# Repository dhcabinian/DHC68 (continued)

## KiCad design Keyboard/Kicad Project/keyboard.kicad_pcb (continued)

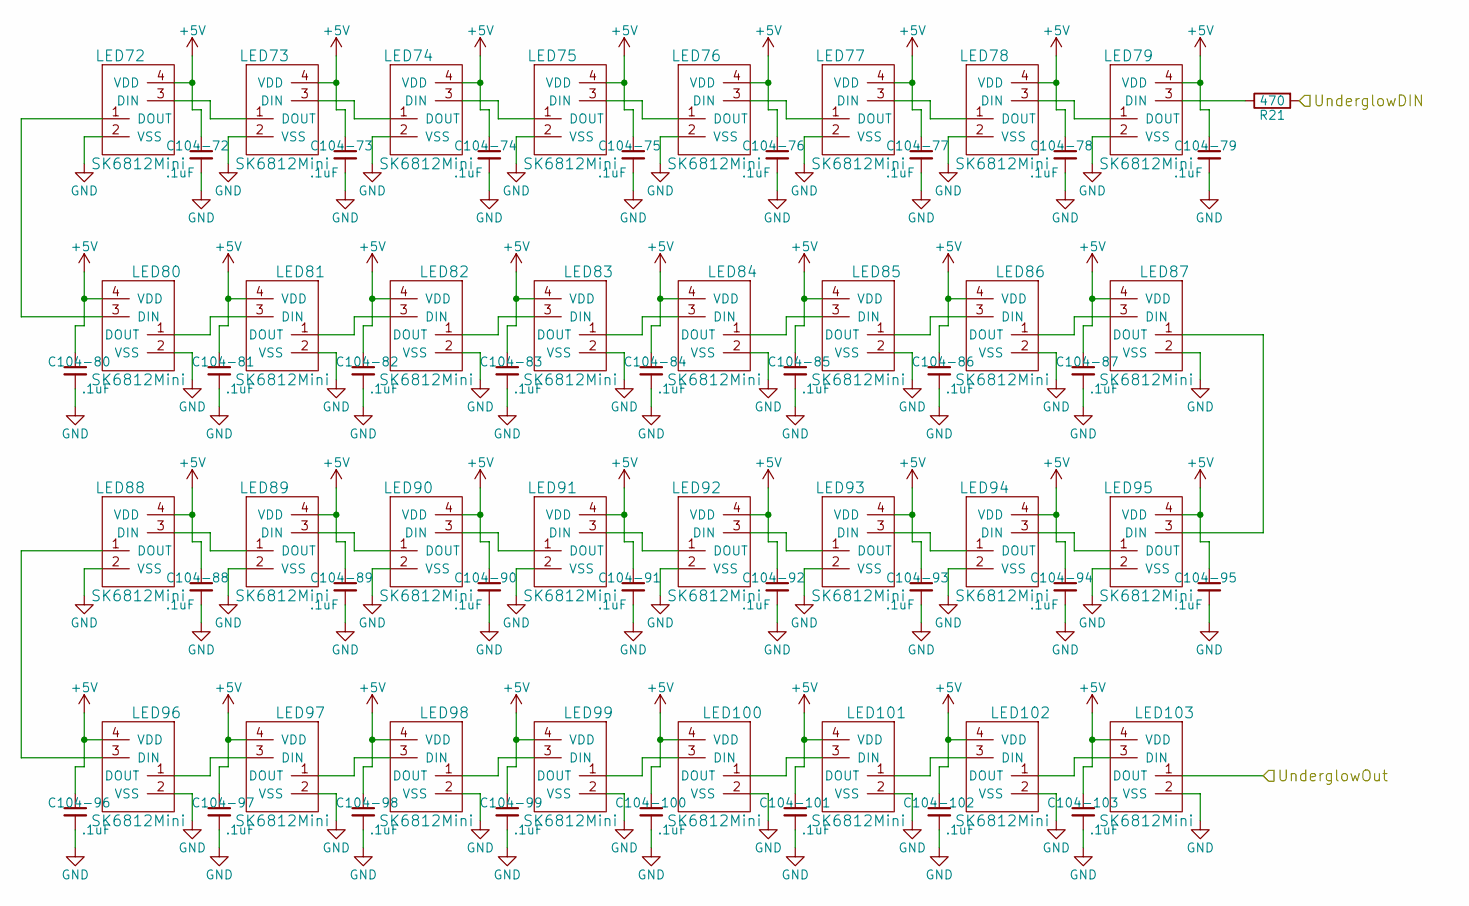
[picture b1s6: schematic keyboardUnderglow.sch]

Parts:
C104-72, C104-73, C104-74, C104-75, C104-76, C104-77, C104-78, C104-79, C104-80, C104-81, C104-82, C104-83, C104-84, C104-85, C104-86, C104-87, C104-88, C104-89, C104-90, C104-91, C104-92, C104-93, C104-94, C104-95, C104-96, C104-97, C104-98, C104-99, C104-100, C104-101, C104-102, C104-103: .1uF; 0805C
LED72, LED73, LED74, LED75, LED76, LED77, LED78, LED79, LED80, LED81, LED82, LED83, LED84, LED85, LED86, LED87, LED88, LED89, LED90, LED91, LED92, LED93, LED94, LED95, LED96, LED97, LED98, LED99, LED100, LED101, LED102, LED103: SK6812Mini; Sk6812Mini
R21: 470; 0805R

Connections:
+5V: C104-72.1, C104-73.1, C104-74.1, C104-75.1, C104-76.1, C104-77.1, C104-78.1, C104-79.1, C104-80.1, C104-81.1, C104-82.1, C104-83.1, C104-84.1, C104-85.1, C104-86.1, C104-87.1, C104-88.1, C104-89.1, C104-90.1, C104-91.1, C104-92.1, C104-93.1, C104-94.1, C104-95.1, C104-96.1, C104-97.1, C104-98.1, C104-99.1, C104-100.1, C104-101.1, C104-102.1, C104-103.1, LED72.4 (VDD), LED73.4 (VDD), LED74.4 (VDD), LED75.4 (VDD), LED76.4 (VDD), LED77.4 (VDD), LED78.4 (VDD), LED79.4 (VDD), LED80.4 (VDD), LED81.4 (VDD), LED82.4 (VDD), LED83.4 (VDD), LED84.4 (VDD), LED85.4 (VDD), LED86.4 (VDD), LED87.4 (VDD), LED88.4 (VDD), LED89.4 (VDD), LED90.4 (VDD), LED91.4 (VDD), LED92.4 (VDD), LED93.4 (VDD), LED94.4 (VDD), LED95.4 (VDD), LED96.4 (VDD), LED97.4 (VDD), LED98.4 (VDD), LED99.4 (VDD), LED100.4 (VDD), LED101.4 (VDD), LED102.4 (VDD), LED103.4 (VDD); also elsewhere on the board
/keyboardUnderglow/UnderglowDIN: R21.2; also elsewhere on the board
/keyboardUnderglow/UnderglowOut: LED103.1 (DOUT); also elsewhere on the board
GND: C104-72.2, C104-73.2, C104-74.2, C104-75.2, C104-76.2, C104-77.2, C104-78.2, C104-79.2, C104-80.2, C104-81.2, C104-82.2, C104-83.2, C104-84.2, C104-85.2, C104-86.2, C104-87.2, C104-88.2, C104-89.2, C104-90.2, C104-91.2, C104-92.2, C104-93.2, C104-94.2, C104-95.2, C104-96.2, C104-97.2, C104-98.2, C104-99.2, C104-100.2, C104-101.2, C104-102.2, C104-103.2, LED72.2 (VSS), LED73.2 (VSS), LED74.2 (VSS), LED75.2 (VSS), LED76.2 (VSS), LED77.2 (VSS), LED78.2 (VSS), LED79.2 (VSS), LED80.2 (VSS), LED81.2 (VSS), LED82.2 (VSS), LED83.2 (VSS), LED84.2 (VSS), LED85.2 (VSS), LED86.2 (VSS), LED87.2 (VSS), LED88.2 (VSS), LED89.2 (VSS), LED90.2 (VSS), LED91.2 (VSS), LED92.2 (VSS), LED93.2 (VSS), LED94.2 (VSS), LED95.2 (VSS), LED96.2 (VSS), LED97.2 (VSS), LED98.2 (VSS), LED99.2 (VSS), LED100.2 (VSS), LED101.2 (VSS), LED102.2 (VSS), LED103.2 (VSS); also elsewhere on the board
unnamed: LED72.1 (DOUT), LED80.3 (DIN)
unnamed: LED72.3 (DIN), LED73.1 (DOUT)
unnamed: LED73.3 (DIN), LED74.1 (DOUT)
unnamed: LED74.3 (DIN), LED75.1 (DOUT)
unnamed: LED75.3 (DIN), LED76.1 (DOUT)
unnamed: LED76.3 (DIN), LED77.1 (DOUT)
unnamed: LED77.3 (DIN), LED78.1 (DOUT)
unnamed: LED78.3 (DIN), LED79.1 (DOUT)
unnamed: LED79.3 (DIN), R21.1
unnamed: LED80.1 (DOUT), LED81.3 (DIN)
unnamed: LED81.1 (DOUT), LED82.3 (DIN)
unnamed: LED82.1 (DOUT), LED83.3 (DIN)
unnamed: LED83.1 (DOUT), LED84.3 (DIN)
unnamed: LED84.1 (DOUT), LED85.3 (DIN)
unnamed: LED85.1 (DOUT), LED86.3 (DIN)
unnamed: LED86.1 (DOUT), LED87.3 (DIN)
unnamed: LED87.1 (DOUT), LED95.3 (DIN)
unnamed: LED88.1 (DOUT), LED96.3 (DIN)
unnamed: LED88.3 (DIN), LED89.1 (DOUT)
unnamed: LED89.3 (DIN), LED90.1 (DOUT)
unnamed: LED90.3 (DIN), LED91.1 (DOUT)
unnamed: LED91.3 (DIN), LED92.1 (DOUT)
unnamed: LED92.3 (DIN), LED93.1 (DOUT)
unnamed: LED93.3 (DIN), LED94.1 (DOUT)
unnamed: LED94.3 (DIN), LED95.1 (DOUT)
unnamed: LED96.1 (DOUT), LED97.3 (DIN)
unnamed: LED97.1 (DOUT), LED98.3 (DIN)
unnamed: LED98.1 (DOUT), LED99.3 (DIN)
unnamed: LED100.1 (DOUT), LED101.3 (DIN)
unnamed: LED99.1 (DOUT), LED100.3 (DIN)
unnamed: LED101.1 (DOUT), LED102.3 (DIN)
unnamed: LED102.1 (DOUT), LED103.3 (DIN)

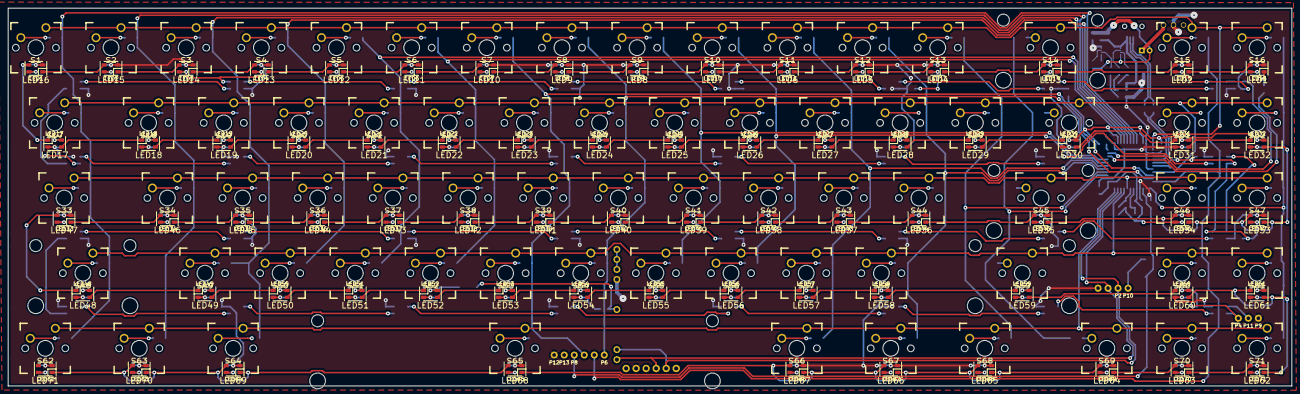
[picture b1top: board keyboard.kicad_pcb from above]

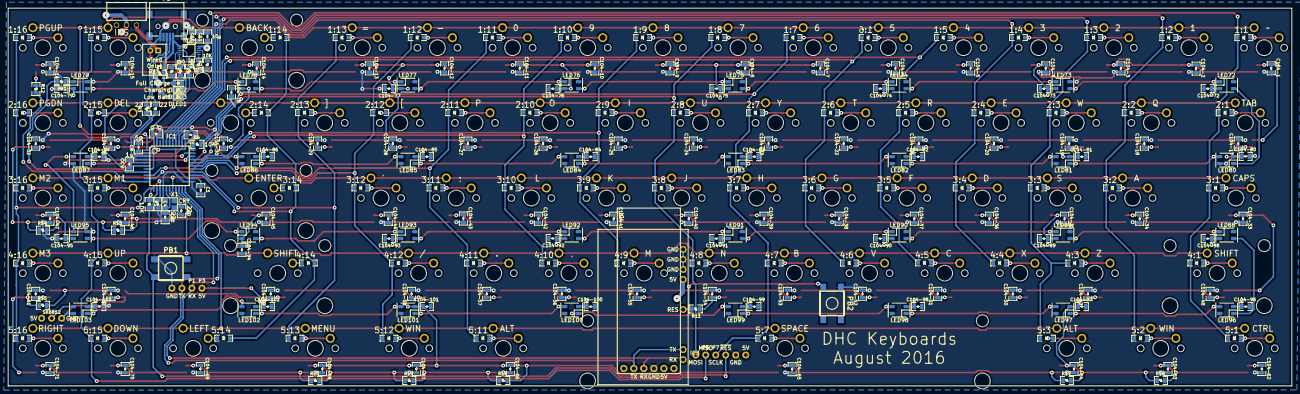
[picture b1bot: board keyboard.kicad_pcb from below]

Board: 2 copper layers, 325.4 x 95.8 mm, 406 parts (255 on the bottom side), 222 nets.

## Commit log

2016-07-31 DHC68 Gerbers + Firmware
